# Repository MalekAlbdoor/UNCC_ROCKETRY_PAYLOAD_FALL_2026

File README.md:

# UNCC Rocketry Payload, Fall 2026

Custom avionics board for the UNC Charlotte rocketry club's transonic payload. It logs flight data, tracks position, sends live telemetry and pad status to a ground station, and controls an onboard camera.

## Layout

The schematic is split into hierarchical sheets, all tied together on the root sheet:

| Sheet | Contents |
|---|---|
| POWER | 5V buck, 3.3V regulator, power LED, bring-up jumpers and camera power switch |
| MCU | Microcontroller, clock, reset/boot, battery voltage sense, buzzer and status LED |
| SENSORS | Inertial, pressure and environmental sensors |
| RF | LoRa telemetry radio and GPS |
| FLASH | Onboard flight data storage |
| CONNECTORS | Battery input protection, arming switch, debug header, camera and USB-C |

Parts, pin map, power and connector pinouts are in [docs/hardware.md](docs/hardware.md).

## Tools

Designed in KiCad 10. Open `UNCC_ROCKETRY_PAYLOAD_FALL_2026.kicad_pro` to get started.

No KiCad? Download [Schematic.pdf](Schematic.pdf) to view the full schematic.

## Board

4-layer, 53.34 x 127.0 mm board, designed to JLCPCB's standard 4-layer rules.

| Top | Bottom |
|---|---|
|  |  |

### PCB layout

Routed copper on all four layers, with silkscreen on the top and bottom (bottom view is mirrored).

All layers together, as shown in the KiCad PCB editor:

## Dashboard
Take a look at live telemetry at telemetry.malekalbdoor.com

## Mechanical

3D models and dimensions for the mechanical team. Everything is in millimetres.

| File | What it is |
|---|---|
| [mechanical/UNCC_ROCKETRY_PAYLOAD_FALL_2026.step](mechanical/UNCC_ROCKETRY_PAYLOAD_FALL_2026.step) | Full board with all components (STEP) |
| [mechanical/UNCC_ROCKETRY_PAYLOAD_FALL_2026_board_only.step](mechanical/UNCC_ROCKETRY_PAYLOAD_FALL_2026_board_only.step) | Bare board, no components (STEP) |
| [mechanical/UNCC_ROCKETRY_PAYLOAD_FALL_2026.stl](mechanical/UNCC_ROCKETRY_PAYLOAD_FALL_2026.stl) | Full board with all components (STL mesh) |
| [mechanical/UNCC_ROCKETRY_PAYLOAD_FALL_2026_board_only.stl](mechanical/UNCC_ROCKETRY_PAYLOAD_FALL_2026_board_only.stl) | Bare board, no components (STL mesh) |
| [mechanical/UNCC_ROCKETRY_PAYLOAD_FALL_2026_outline.dxf](mechanical/UNCC_ROCKETRY_PAYLOAD_FALL_2026_outline.dxf) | Board outline for CAD (DXF) |
| [images/board_dimensions.svg](images/board_dimensions.svg) | Dimensioned drawing with mounting holes and connector positions |

| Item | Value |
|---|---|
| Board size | 53.34 x 127.0 mm, corner radius 3.05 mm |
| Board thickness | 1.6 mm |
| Mounting holes | 4 x 3.2 mm (M3), 5.08 mm in from each side edge and 5.08 mm in from the short edges |
| Hole positions (x, y from top-left corner) | (5.08, 5.08), (48.26, 5.08), (5.08, 121.92), (48.26, 121.92) |
| Tallest part on top | about 9.2 mm above the board, the three screw terminals on the right edge |
| Other parts on top | up to about 7 mm above the board |
| Lead tails under the board | about 2.9 mm below the bottom face (screw terminals), 1.8 mm elsewhere |
| Connectors on the edges | USB-C and two battery/switch JSTs on the bottom short edge, three camera JSTs and the VTX JST on the left edge, three screw terminals on the right edge |

Heights come from the KiCad 3D models, so check them against the part datasheets before you design a tight enclosure. Connector positions are listed on the dimensioned drawing.

## Status

PCB layout is routed and passes design rules; only silkscreen warnings remain. Firmware is being developed on breadboarded breakout boards in parallel.

## License

Copyright (c) 2026 Malek Albdoor.

Everything in this repository (schematics, PCB layout, 3D models, firmware and the telemetry dashboard) is licensed under [Creative Commons Attribution-NonCommercial 4.0](LICENSE) (CC BY-NC 4.0).

- **You can** use, copy, modify and share it for noncommercial purposes, such as personal projects, school teams and research.
- **You must** credit both Malek Albdoor and the [Charlotte Rocketry Club](https://www.charlotterocketry.org/) at UNC Charlotte, link back to this repository, and say if you changed anything.
- **You cannot** use it, or anything made from it, to make money without written permission.

Credit it like this:

> Based on the UNCC Rocketry payload board by Malek Albdoor and the Charlotte Rocketry Club at UNC Charlotte (https://www.charlotterocketry.org/), https://github.com/MalekAlbdoor/UNCC_ROCKETRY_PAYLOAD_FALL_2026, CC BY-NC 4.0.

Libraries and KiCad library parts used by this project keep their own licenses.

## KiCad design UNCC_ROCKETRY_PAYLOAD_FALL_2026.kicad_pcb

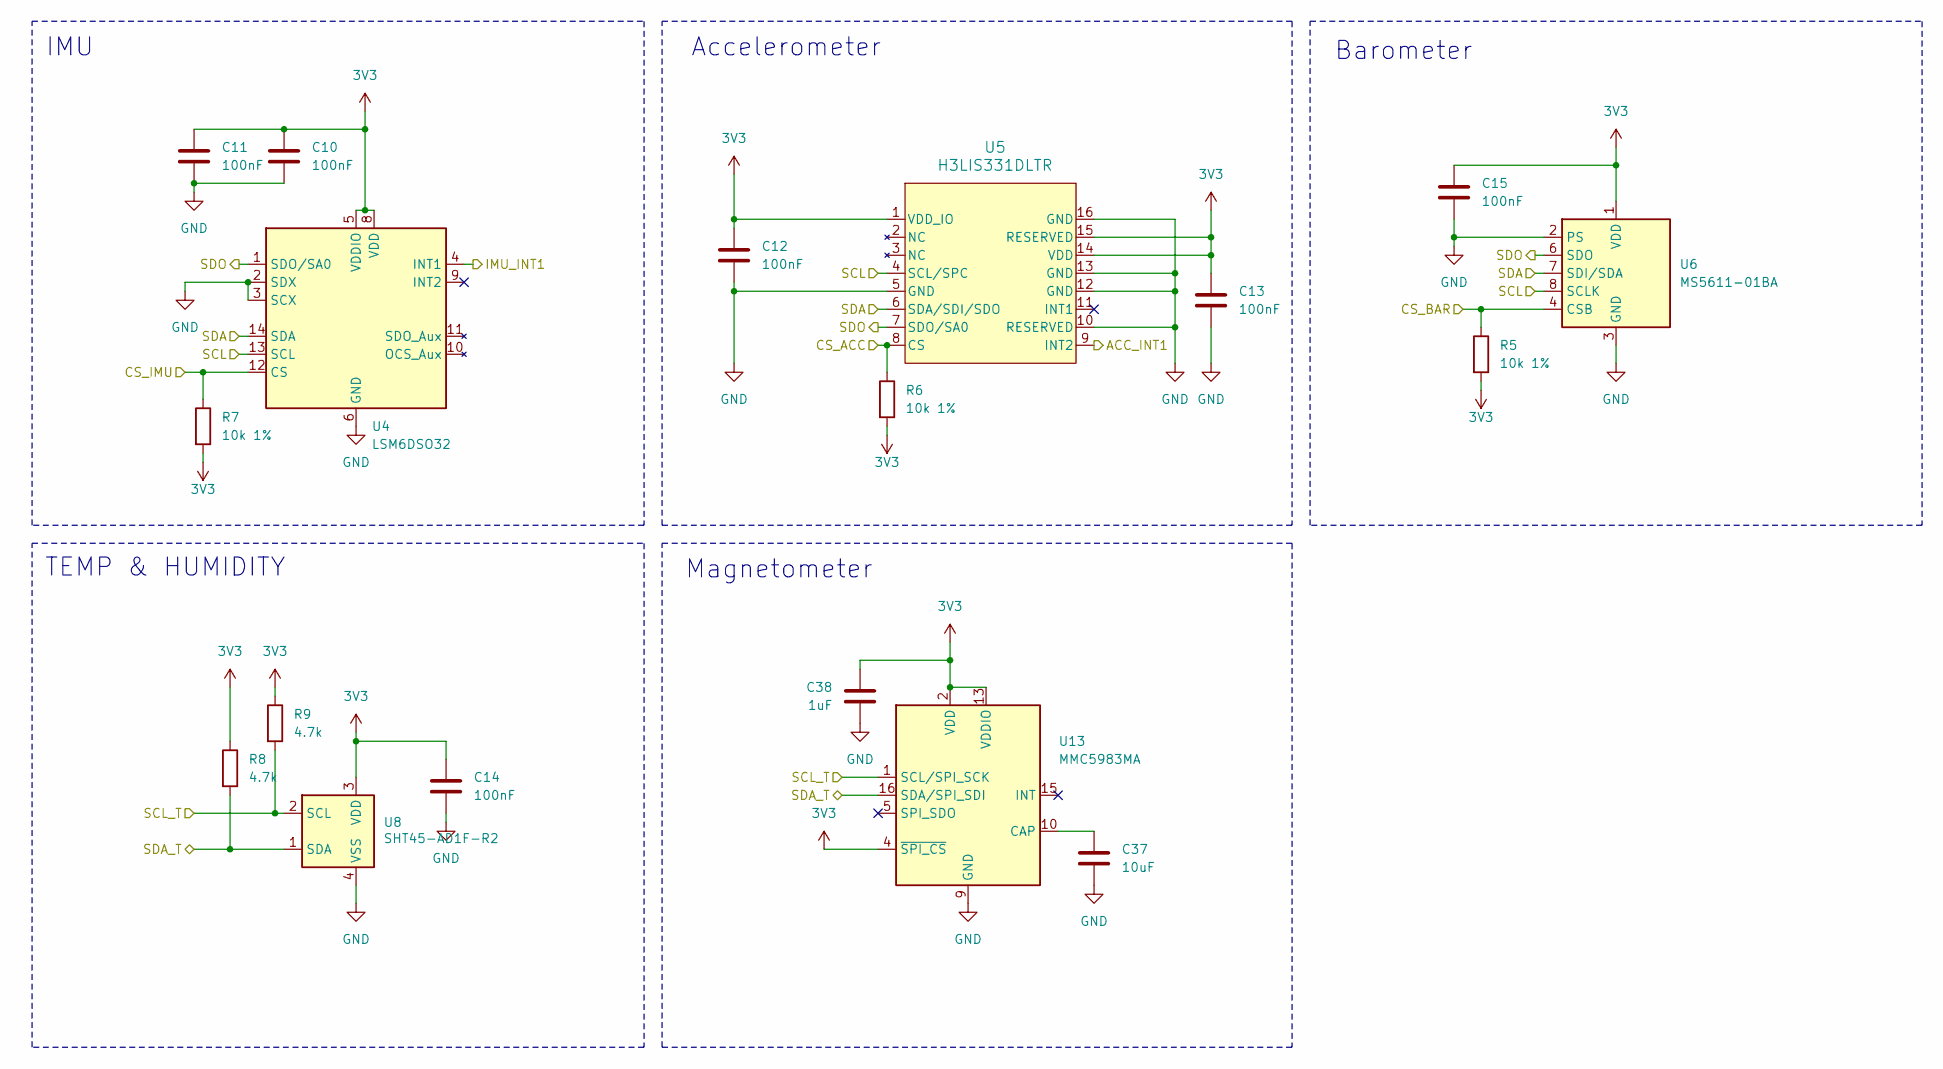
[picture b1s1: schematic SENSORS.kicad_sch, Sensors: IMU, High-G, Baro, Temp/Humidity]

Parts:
C10, C11, C12, C13, C14, C15: 100nF; C_0603_1608Metric_Pad1.08x0.95mm_HandSolder; MPN CC0603KRX7R9BB104; LCSC C14663
C37: 10uF; C_0805_2012Metric_Pad1.18x1.45mm_HandSolder; MPN CL21A106KAYNNNE; LCSC C15850
C38: 1uF; C_0603_1608Metric_Pad1.08x0.95mm_HandSolder; MPN CL10A105KB8NNNC; LCSC C15849
R5, R6, R7: 10k 1%; R_0603_1608Metric_Pad0.98x0.95mm_HandSolder; MPN 0603WAF1002T5E; LCSC C25804
R8, R9: 4.7k; R_0603_1608Metric_Pad0.98x0.95mm_HandSolder; MPN 0603WAF4701T5E; LCSC C23162
U4: LSM6DSO32; LGA-14_3x2.5mm_P0.5mm_LayoutBorder3x4y; MPN LSM6DSO32XTR; LCSC C3663738
U5: H3LIS331DLTR; LGA-16_3x3mm_P0.5mm_LayoutBorder3x5y; MPN H3LIS331DLTR; LCSC C2655074
U6: MS5611-01BA; LGA-8_3x5mm_P1.25mm; MPN MS5611-01BA03; LCSC C37148
U8: SHT45-AD1F-R2; Sensirion_DFN-4_1.5x1.5mm_P0.8mm_SHT4x_NoCentralPad; MPN SHT45-AD1F-R2; LCSC C5360602
U13: MMC5983MA; LGA-16_3x3mm_P0.5mm; MPN MMC5983MA; LCSC C404329

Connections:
3V3: C10.1, C11.1, C12.1, C13.1, C14.1, C15.1, C38.1, R5.2, R6.2, R7.2, R8.1, R9.1, U4.5 (VDDIO), U4.8 (VDD), U5.1 (VDD_IO), U5.14 (VDD), U5.15 (RESERVED), U6.1 (VDD), U8.3 (VDD), U13.2 (VDD), U13.4 (~SPI_CS), U13.13 (VDDIO); also elsewhere on the board
/MCU/ACC_INT1: U5.9 (INT2); also elsewhere on the board
/MCU/CS_ACC: R6.1, U5.8 (CS); also elsewhere on the board
/MCU/CS_BAR: R5.1, U6.4 (CSB), U6.5 (CSB); also elsewhere on the board
/MCU/CS_IMU: R7.1, U4.12 (CS); also elsewhere on the board
/MCU/IMU_INT1: U4.4 (INT1); also elsewhere on the board
/MCU/SCL: U4.13 (SCL), U5.4 (SCL/SPC), U6.8 (SCLK); also elsewhere on the board
/MCU/SDA: U4.14 (SDA), U5.6 (SDA/SDI/SDO), U6.7 (SDI/SDA); also elsewhere on the board
/MCU/SDO: U4.1 (SDO/SA0), U5.7 (SDO/SA0), U6.6 (SDO); also elsewhere on the board
/SCL_T: R9.2, U8.2 (SCL), U13.1 (SCL/SPI_SCK); also elsewhere on the board
/SDA_T: R8.2, U8.1 (SDA), U13.16 (SDA/SPI_SDI); also elsewhere on the board
GND: C10.2, C11.2, C12.2, C13.2, C14.2, C15.2, C37.2, C38.2, U4.2 (SDX), U4.3 (SCX), U4.6 (GND), U4.7 (GND), U5.5 (GND), U5.10 (RESERVED), U5.12 (GND), U5.13 (GND), U5.16 (GND), U6.2 (PS), U6.3 (GND), U8.4 (VSS), U13.9 (GND), U13.11 (GND); also elsewhere on the board
unnamed: C37.1, U13.10 (CAP)

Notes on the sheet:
Magnetometer
TEMP & HUMIDITY
Barometer
Accelerometer
IMU

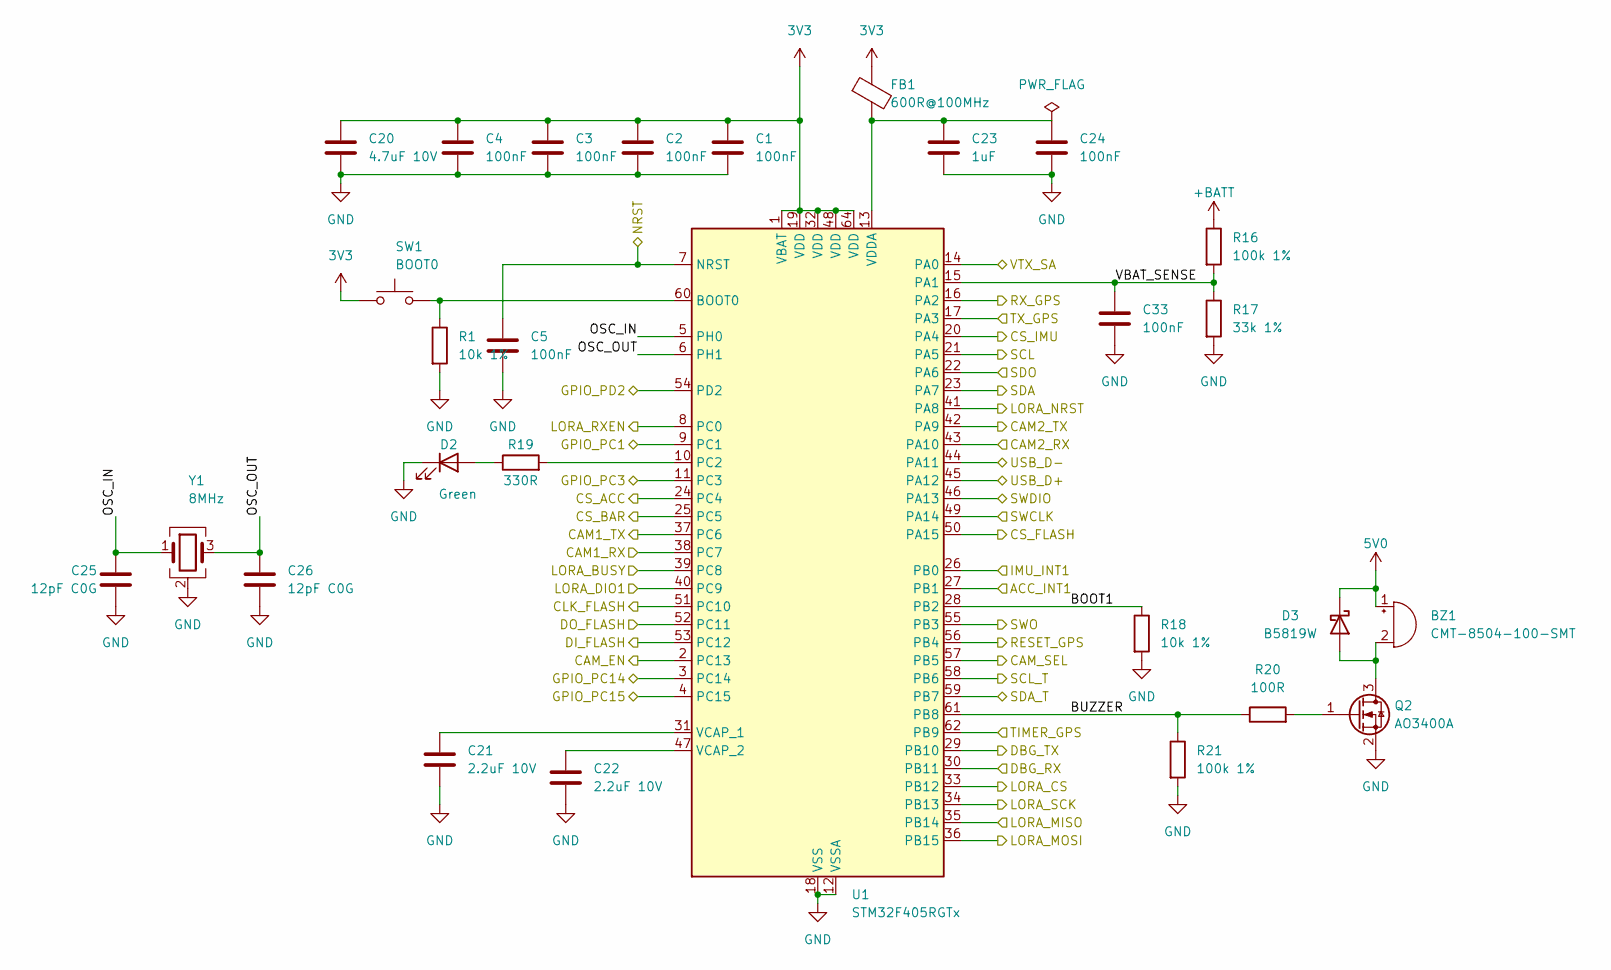
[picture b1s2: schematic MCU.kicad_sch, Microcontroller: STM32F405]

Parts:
BZ1: CMT-8504-100-SMT; MagneticBuzzer_CUI_CMT-8504-100-SMT; MPN CMT-8504-100-SMT-TR; LCSC C22359707
C1, C2, C3, C4, C5, C24, C33: 100nF; C_0603_1608Metric_Pad1.08x0.95mm_HandSolder; MPN CC0603KRX7R9BB104; LCSC C14663
C20: 4.7uF 10V; C_0603_1608Metric_Pad1.08x0.95mm_HandSolder; MPN CL10A475KO8NNNC; LCSC C19666
C21, C22: 2.2uF 10V; C_0603_1608Metric_Pad1.08x0.95mm_HandSolder; MPN CL10A225KO8NNNC; LCSC C23630
C23: 1uF; C_0603_1608Metric_Pad1.08x0.95mm_HandSolder; MPN CL10A105KB8NNNC; LCSC C15849
C25, C26: 12pF C0G; C_0603_1608Metric_Pad1.08x0.95mm_HandSolder; MPN CL10C120JB8NNNC; LCSC C38523
D2: Green; LED_0603_1608Metric_Pad1.05x0.95mm_HandSolder; MPN 19-217/G7C-AN1P2/6T; LCSC C2986030
D3: B5819W; D_SOD-123; MPN B5819W; LCSC C7420330
FB1: 600R@100MHz; L_0603_1608Metric_Pad1.05x0.95mm_HandSolder; MPN GZ1608D601TF; LCSC C1002
Q2: AO3400A; SOT-23; MPN AO3400A; LCSC C20917
R1, R18: 10k 1%; R_0603_1608Metric_Pad0.98x0.95mm_HandSolder; MPN 0603WAF1002T5E; LCSC C25804
R16, R21: 100k 1%; R_0603_1608Metric_Pad0.98x0.95mm_HandSolder; MPN 0603WAF1003T5E; LCSC C25803
R17: 33k 1%; R_0603_1608Metric_Pad0.98x0.95mm_HandSolder; MPN 0603WAF3302T5E; LCSC C4216
R19: 330R; R_0603_1608Metric_Pad0.98x0.95mm_HandSolder; MPN 0603WAF3300T5E; LCSC C23138
R20: 100R; R_0603_1608Metric_Pad0.98x0.95mm_HandSolder; MPN 0603WAF1000T5E; LCSC C22775
SW1: BOOT0; SW_SPST_TL3342; MPN TL3342F450QG; LCSC C2886897
U1: STM32F405RGTx; LQFP-64_10x10mm_P0.5mm; MPN STM32F405RGT6; LCSC C15742
Y1: 8MHz; Crystal_SMD_Abracon_ABM3B-4Pin_5.0x3.2mm; MPN ABM3B-8.000MHZ-10-D-1-G-T; LCSC C1985378

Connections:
3V3: C1.1, C2.1, C3.1, C4.1, C20.1, FB1.1, SW1.1, U1.1 (VBAT), U1.19 (VDD), U1.32 (VDD), U1.48 (VDD), U1.64 (VDD); also elsewhere on the board
5V0: BZ1.1 (+), D3.1 (K); also elsewhere on the board
+BATT: R16.1; also elsewhere on the board
/CONNECTORS/CAM1_RX: U1.38 (PC7); also elsewhere on the board
/CONNECTORS/CAM1_TX: U1.37 (PC6); also elsewhere on the board
/CONNECTORS/CAM2_RX: U1.43 (PA10); also elsewhere on the board
/CONNECTORS/CAM2_TX: U1.42 (PA9); also elsewhere on the board
/CONNECTORS/CAM_SEL: U1.57 (PB5); also elsewhere on the board
/CONNECTORS/DBG_RX: U1.30 (PB11); also elsewhere on the board
/CONNECTORS/DBG_TX: U1.29 (PB10); also elsewhere on the board
/CONNECTORS/GPIO_PC1: U1.9 (PC1); also elsewhere on the board
/CONNECTORS/GPIO_PC3: U1.11 (PC3); also elsewhere on the board
/CONNECTORS/GPIO_PC14: U1.3 (PC14); also elsewhere on the board
/CONNECTORS/GPIO_PC15: U1.4 (PC15); also elsewhere on the board
/CONNECTORS/NRST: C5.1, U1.7 (NRST); also elsewhere on the board
/CONNECTORS/SWCLK: U1.49 (PA14); also elsewhere on the board
/CONNECTORS/SWDIO: U1.46 (PA13); also elsewhere on the board
/CONNECTORS/SWO: U1.55 (PB3); also elsewhere on the board
/CONNECTORS/USB_D+: U1.45 (PA12); also elsewhere on the board
/CONNECTORS/USB_D-: U1.44 (PA11); also elsewhere on the board
/CONNECTORS/VTX_SA: U1.14 (PA0); also elsewhere on the board
/FLASH/CLK_FLASH: U1.51 (PC10); also elsewhere on the board
/FLASH/CS_FLASH: U1.50 (PA15); also elsewhere on the board
/FLASH/DI_FLASH: U1.53 (PC12); also elsewhere on the board
/FLASH/DO_FLASH: U1.52 (PC11); also elsewhere on the board
/MCU/ACC_INT1: U1.27 (PB1); also elsewhere on the board
/MCU/BOOT1: R18.1, U1.28 (PB2)
/MCU/BUZZER: R20.1, R21.1, U1.61 (PB8)
/MCU/CAM_EN: U1.2 (PC13); also elsewhere on the board
/MCU/CS_ACC: U1.24 (PC4); also elsewhere on the board
/MCU/CS_BAR: U1.25 (PC5); also elsewhere on the board
/MCU/CS_IMU: U1.20 (PA4); also elsewhere on the board
/MCU/GPIO_PD2: U1.54 (PD2)
/MCU/IMU_INT1: U1.26 (PB0); also elsewhere on the board
/MCU/LORA_BUSY: U1.39 (PC8); also elsewhere on the board
/MCU/LORA_CS: U1.33 (PB12); also elsewhere on the board
/MCU/LORA_DIO1: U1.40 (PC9); also elsewhere on the board
/MCU/LORA_MISO: U1.35 (PB14); also elsewhere on the board
/MCU/LORA_MOSI: U1.36 (PB15); also elsewhere on the board
/MCU/LORA_NRST: U1.41 (PA8); also elsewhere on the board
/MCU/LORA_RXEN: U1.8 (PC0); also elsewhere on the board
/MCU/LORA_SCK: U1.34 (PB13); also elsewhere on the board
/MCU/OSC_IN: C25.1, U1.5 (PH0), Y1.1
/MCU/OSC_OUT: C26.1, U1.6 (PH1), Y1.3
/MCU/RESET_GPS: U1.56 (PB4); also elsewhere on the board
/MCU/RX_GPS: U1.16 (PA2); also elsewhere on the board
/MCU/SCL: U1.21 (PA5); also elsewhere on the board
/MCU/SDA: U1.23 (PA7); also elsewhere on the board
/MCU/SDO: U1.22 (PA6); also elsewhere on the board
/MCU/TIMER_GPS: U1.62 (PB9); also elsewhere on the board
/MCU/TX_GPS: U1.17 (PA3); also elsewhere on the board
/MCU/VBAT_SENSE: C33.1, R16.2, R17.1, U1.15 (PA1)
/SCL_T: U1.58 (PB6); also elsewhere on the board
/SDA_T: U1.59 (PB7); also elsewhere on the board
GND: C1.2, C2.2, C3.2, C4.2, C5.2, C20.2, C21.2, C22.2, C23.2, C24.2, C25.2, C26.2, C33.2, D2.1 (K), Q2.2 (S), R1.2, R17.2, R18.2, R21.2, U1.12 (VSSA), U1.18 (VSS), U1.63 (VSS), Y1.2 (G), Y1.4 (G); also elsewhere on the board
unnamed: BZ1.2 (-), D3.2 (A), Q2.3 (D)
unnamed: D2.2 (A), R19.1
unnamed: Q2.1 (G), R20.2
unnamed: R1.1, SW1.2, U1.60 (BOOT0)
unnamed: R19.2, U1.10 (PC2)
unnamed: C21.1, U1.31 (VCAP_1)
unnamed: C22.1, U1.47 (VCAP_2)
unnamed: C23.1, C24.1, FB1.2, U1.13 (VDDA)

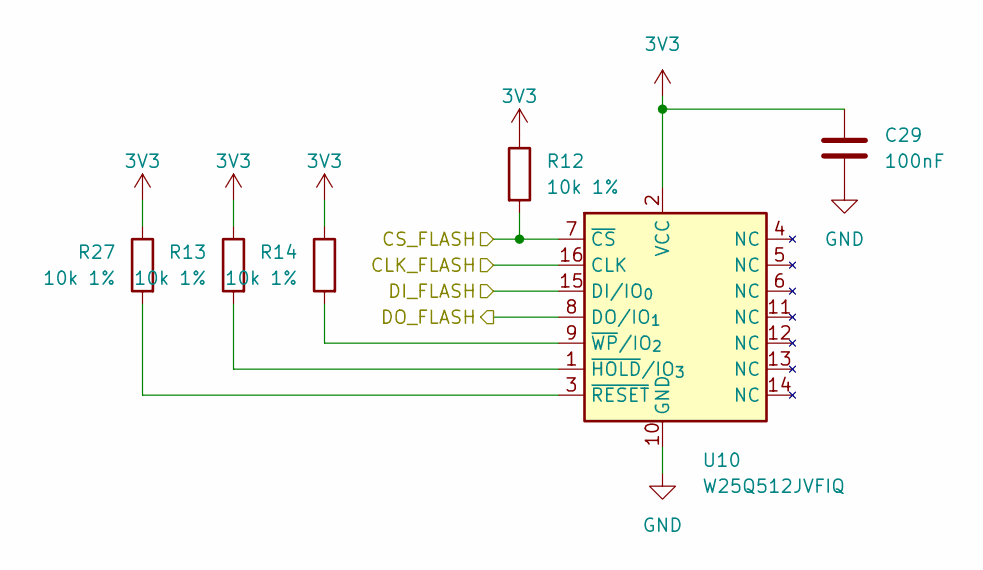
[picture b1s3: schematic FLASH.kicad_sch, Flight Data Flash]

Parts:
C29: 100nF; C_0603_1608Metric_Pad1.08x0.95mm_HandSolder; MPN CC0603KRX7R9BB104; LCSC C14663
R12, R13, R14, R27: 10k 1%; R_0603_1608Metric_Pad0.98x0.95mm_HandSolder; MPN 0603WAF1002T5E; LCSC C25804
U10: W25Q512JVFIQ; SOIC-16W_7.5x10.3mm_P1.27mm; MPN W25Q512JVFIQ; LCSC C2962011

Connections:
3V3: C29.1, R12.1, R13.1, R14.1, R27.1, U10.2 (VCC); also elsewhere on the board
/FLASH/CLK_FLASH: U10.16 (CLK); also elsewhere on the board
/FLASH/CS_FLASH: R12.2, U10.7 (~CS); also elsewhere on the board
/FLASH/DI_FLASH: U10.15 (DI/IO_{0}); also elsewhere on the board
/FLASH/DO_FLASH: U10.8 (DO/IO_{1}); also elsewhere on the board
GND: C29.2, U10.10 (GND); also elsewhere on the board
unnamed: R13.2, U10.1 (~HOLD/IO_{3})
unnamed: R27.2, U10.3 (~RESET)
unnamed: R14.2, U10.9 (~WP/IO_{2})

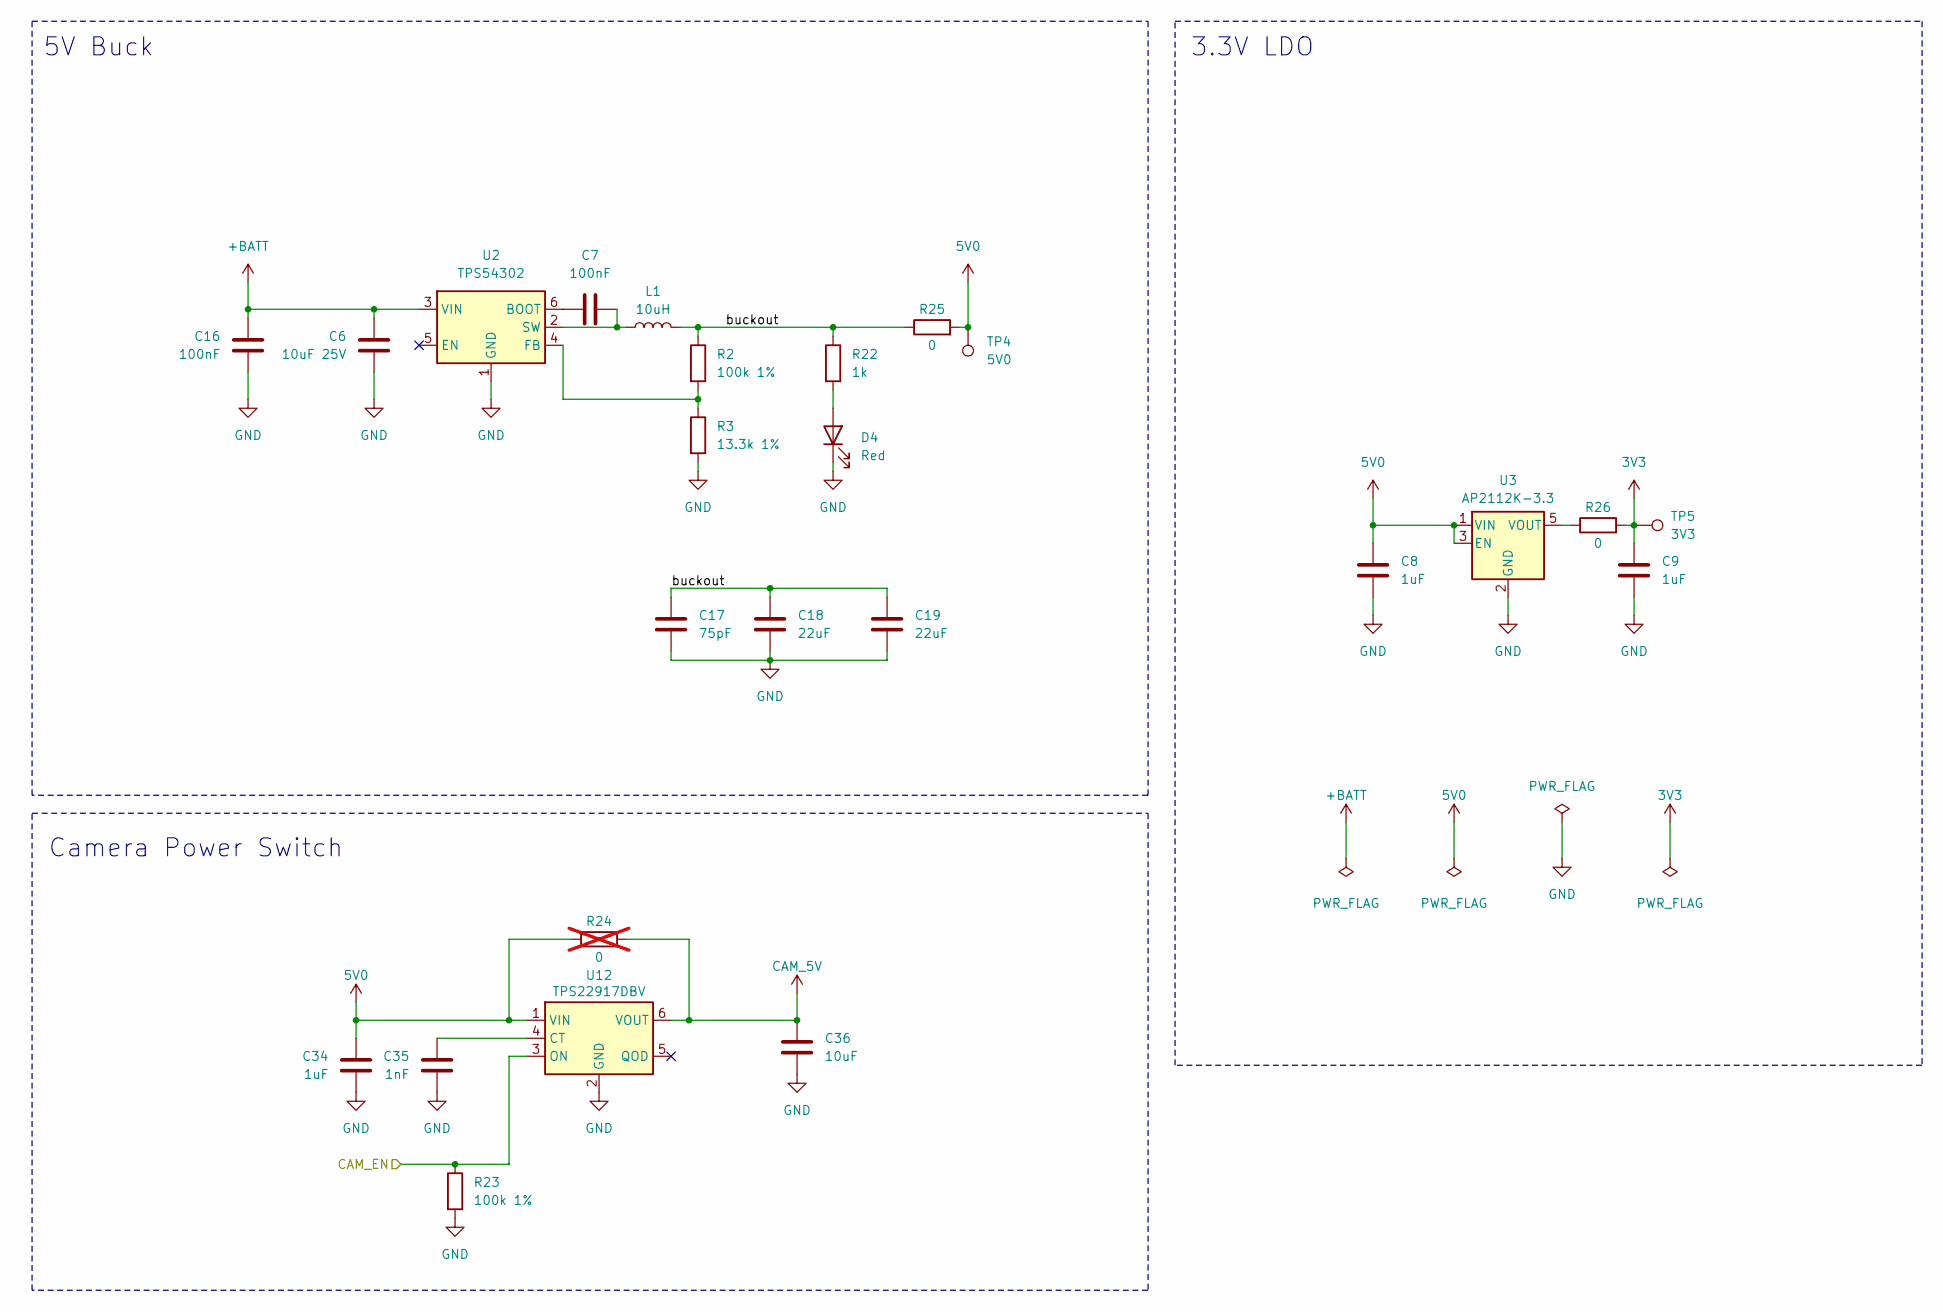
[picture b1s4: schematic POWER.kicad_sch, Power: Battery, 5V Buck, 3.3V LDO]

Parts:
C6: 10uF 25V; C_1206_3216Metric_Pad1.33x1.80mm_HandSolder; MPN CL31A106KBHNNNE; LCSC C13585
C7, C16: 100nF; C_0603_1608Metric_Pad1.08x0.95mm_HandSolder; MPN CC0603KRX7R9BB104; LCSC C14663
C8, C9, C34: 1uF; C_0603_1608Metric_Pad1.08x0.95mm_HandSolder; MPN CL10A105KB8NNNC; LCSC C15849
C17: 75pF; C_0603_1608Metric_Pad1.08x0.95mm_HandSolder; MPN CC0603JRNPO9BN750; LCSC C282074
C18, C19: 22uF; C_1206_3216Metric_Pad1.33x1.80mm_HandSolder; MPN CL31A226KAHNNNE; LCSC C12891
C35: 1nF; C_0603_1608Metric_Pad1.08x0.95mm_HandSolder; MPN CL10B102KB8NNNC; LCSC C1588
C36: 10uF; C_0805_2012Metric_Pad1.18x1.45mm_HandSolder; MPN CL21A106KAYNNNE; LCSC C15850
D4: Red; LED_0603_1608Metric_Pad1.05x0.95mm_HandSolder; MPN KT-0603R; LCSC C2286
L1: 10uH; L_Wuerth_XHMI-6060; MPN 74439346100; LCSC C2651185
R2, R23: 100k 1%; R_0603_1608Metric_Pad0.98x0.95mm_HandSolder; MPN 0603WAF1003T5E; LCSC C25803
R3: 13.3k 1%; R_0603_1608Metric_Pad0.98x0.95mm_HandSolder; MPN 0603WAF1332T5E; LCSC C25952
R22: 1k; R_0603_1608Metric_Pad0.98x0.95mm_HandSolder; MPN 0603WAF1001T5E; LCSC C21190
R24: 0; R_0603_1608Metric_Pad0.98x0.95mm_HandSolder; MPN 0603WAF0000T5E; LCSC C21189; not fitted
R25, R26: 0; R_0603_1608Metric_Pad0.98x0.95mm_HandSolder; MPN 0603WAF0000T5E; LCSC C21189
TP4: 5V0; TestPoint_Pad_D1.5mm
TP5: 3V3; TestPoint_Pad_D1.5mm
U2: TPS54302; SOT-23-6; MPN TPS54302DDCR; LCSC C311983
U3: AP2112K-3.3; SOT-23-5; MPN AP2112K-3.3TRG1; LCSC C23380830
U12: TPS22917DBV; SOT-23-6; MPN TPS22917DBVR; LCSC C2681320

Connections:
3V3: C9.1, R26.2, TP5.1 (1_1); also elsewhere on the board
5V0: C8.1, C34.1, R24.1, R25.2, TP4.1 (1_1), U3.1 (VIN), U3.3 (EN), U12.1 (VIN); also elsewhere on the board
+BATT: C6.1, C16.1, U2.3 (VIN); also elsewhere on the board
/MCU/CAM_EN: R23.1, U12.3 (ON); also elsewhere on the board
/POWER/buckout: C17.1, C18.1, C19.1, L1.2, R2.1, R22.1, R25.1
CAM_5V: C36.1, R24.2, U12.6 (VOUT); also elsewhere on the board
GND: C6.2, C8.2, C9.2, C16.2, C17.2, C18.2, C19.2, C34.2, C35.2, C36.2, D4.1 (K), R3.2, R23.2, U2.1 (GND), U3.2 (GND), U12.2 (GND); also elsewhere on the board
unnamed: D4.2 (A), R22.2
unnamed: C7.1, U2.6 (BOOT)
unnamed: R2.2, R3.1, U2.4 (FB)
unnamed: C7.2, L1.1, U2.2 (SW)
unnamed: R26.1, U3.5 (VOUT)
unnamed: C35.1, U12.4 (CT)

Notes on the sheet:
3.3V LDO
5V Buck
Camera Power Switch

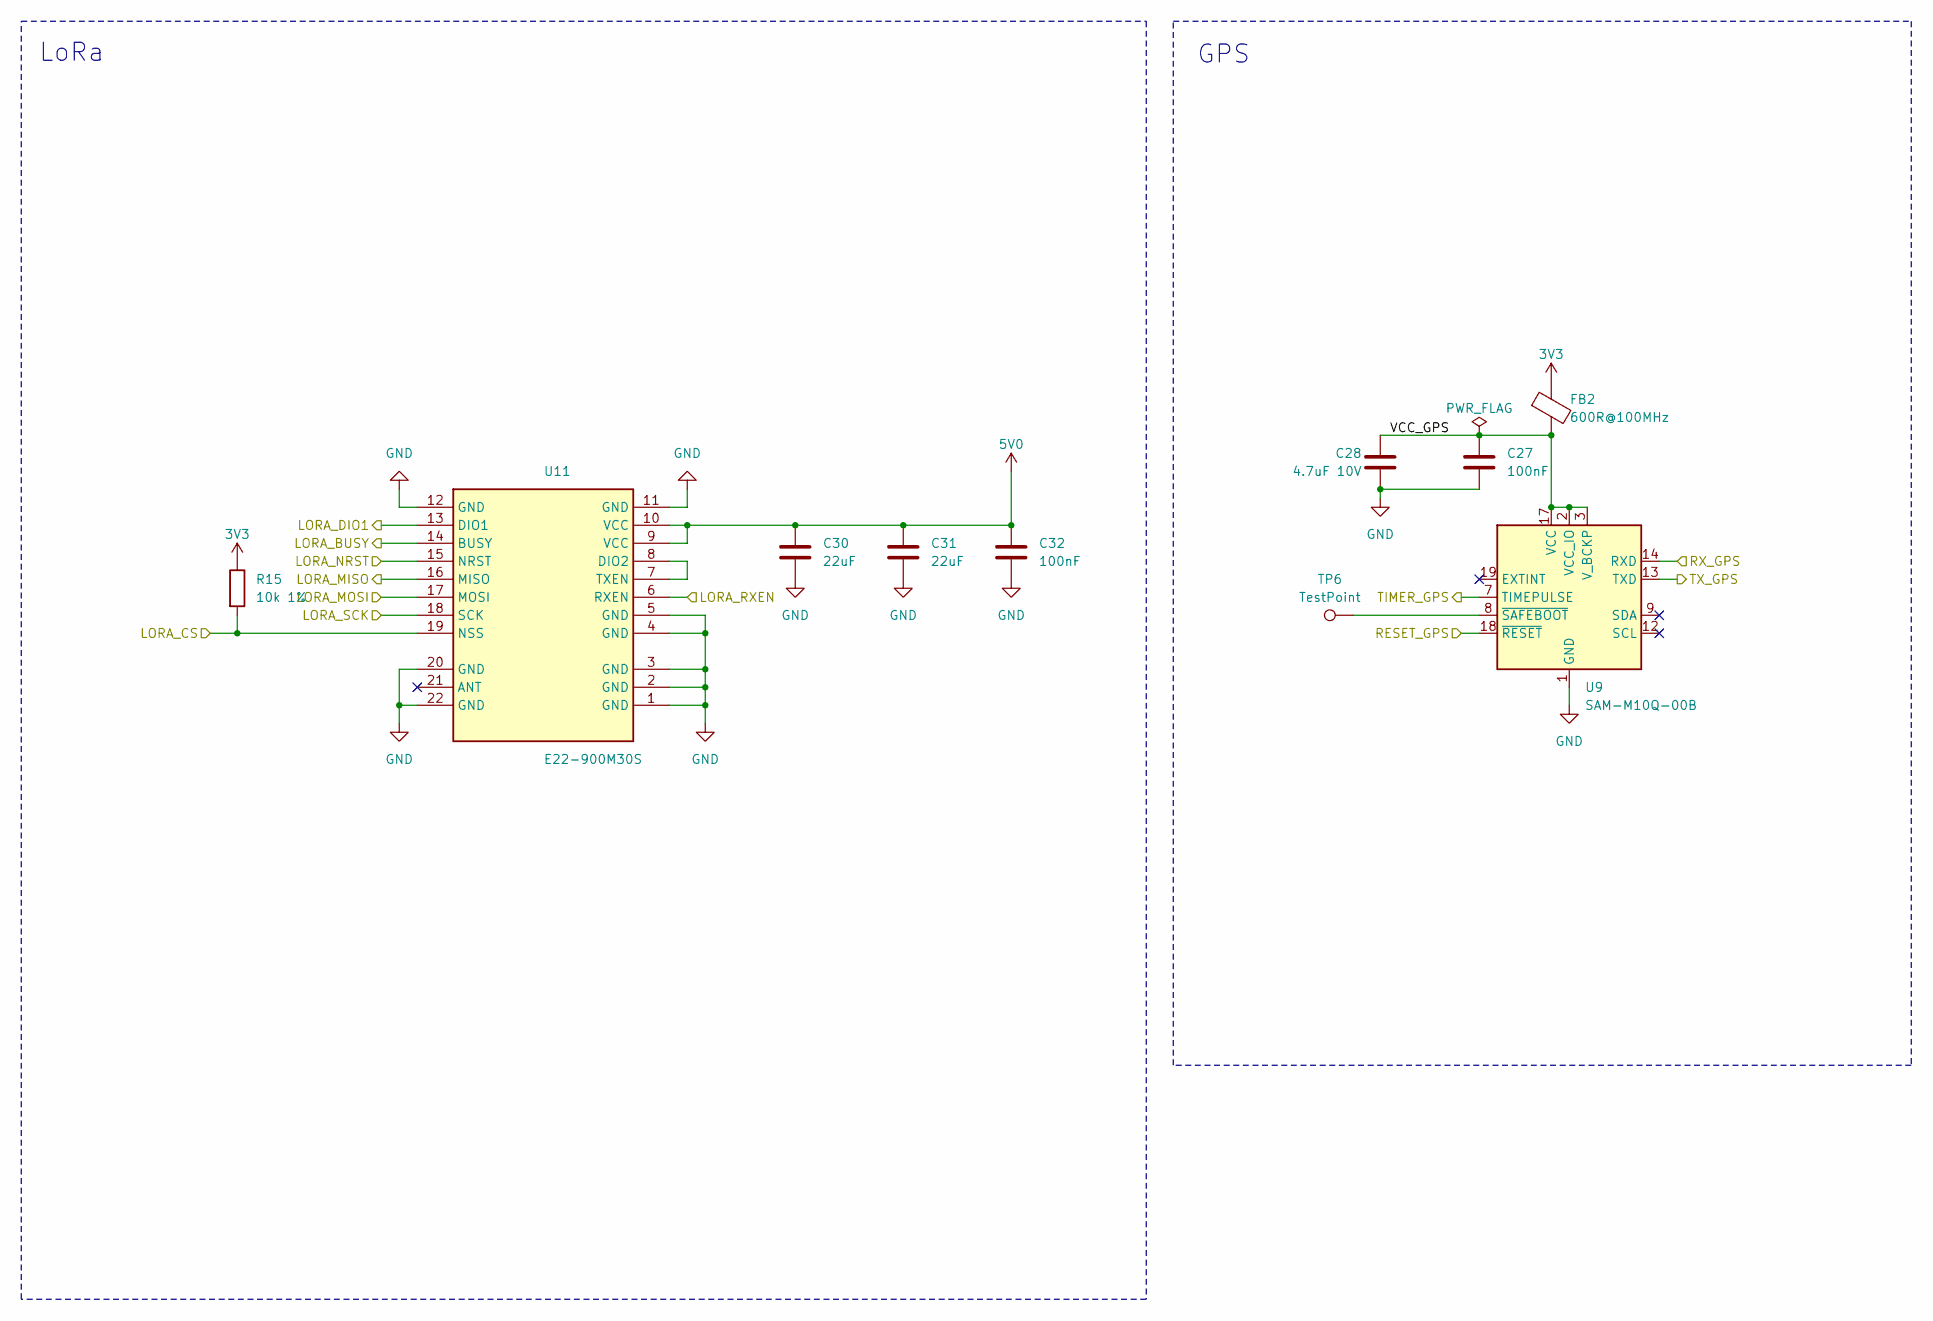
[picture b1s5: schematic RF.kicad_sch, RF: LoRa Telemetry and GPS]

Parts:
C27, C32: 100nF; C_0603_1608Metric_Pad1.08x0.95mm_HandSolder; MPN CC0603KRX7R9BB104; LCSC C14663
C28: 4.7uF 10V; C_0603_1608Metric_Pad1.08x0.95mm_HandSolder; MPN CL10A475KO8NNNC; LCSC C19666
C30, C31: 22uF; C_1206_3216Metric_Pad1.33x1.80mm_HandSolder; MPN CL31A226KAHNNNE; LCSC C12891
FB2: 600R@100MHz; L_0603_1608Metric_Pad1.05x0.95mm_HandSolder; MPN GZ1608D601TF; LCSC C1002
R15: 10k 1%; R_0603_1608Metric_Pad0.98x0.95mm_HandSolder; MPN 0603WAF1002T5E; LCSC C25804
TP6: TestPoint; TestPoint_Pad_D1.5mm
U9: SAM-M10Q-00B; ublox_SAM-M8Q; MPN SAM-M10Q-00B; LCSC C5443880
U11: E22-900M30S; WIRELM-SMD_E22-900M30S; MPN E22-900M30S; LCSC C411294

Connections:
3V3: FB2.1, R15.1; also elsewhere on the board
5V0: C30.1, C31.1, C32.1, U11.9 (VCC), U11.10 (VCC); also elsewhere on the board
/MCU/LORA_BUSY: U11.14 (BUSY); also elsewhere on the board
/MCU/LORA_CS: R15.2, U11.19 (NSS); also elsewhere on the board
/MCU/LORA_DIO1: U11.13 (DIO1); also elsewhere on the board
/MCU/LORA_MISO: U11.16 (MISO); also elsewhere on the board
/MCU/LORA_MOSI: U11.17 (MOSI); also elsewhere on the board
/MCU/LORA_NRST: U11.15 (NRST); also elsewhere on the board
/MCU/LORA_RXEN: U11.6 (RXEN); also elsewhere on the board
/MCU/LORA_SCK: U11.18 (SCK); also elsewhere on the board
/MCU/RESET_GPS: U9.18 (~RESET); also elsewhere on the board
/MCU/RX_GPS: U9.14 (RXD); also elsewhere on the board
/MCU/TIMER_GPS: U9.7 (TIMEPULSE); also elsewhere on the board
/MCU/TX_GPS: U9.13 (TXD); also elsewhere on the board
/RF/VCC_GPS: C27.1, C28.1, FB2.2, U9.2 (VCC_IO), U9.3 (V_BCKP), U9.17 (VCC)
GND: C27.2, C28.2, C30.2, C31.2, C32.2, U9.1 (GND), U9.4 (GND), U9.5 (GND), U9.6 (GND), U9.10 (GND), U9.11 (GND), U9.15 (GND), U9.16 (GND), U9.20 (GND), U11.1 (GND), U11.2 (GND), U11.3 (GND), U11.4 (GND), U11.5 (GND), U11.11 (GND), U11.12 (GND), U11.20 (GND), U11.22 (GND); also elsewhere on the board
unnamed: TP6.1 (1_1), U9.8 (~SAFEBOOT)
unnamed: U11.7 (TXEN), U11.8 (DIO2)

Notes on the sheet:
LoRa
GPS
